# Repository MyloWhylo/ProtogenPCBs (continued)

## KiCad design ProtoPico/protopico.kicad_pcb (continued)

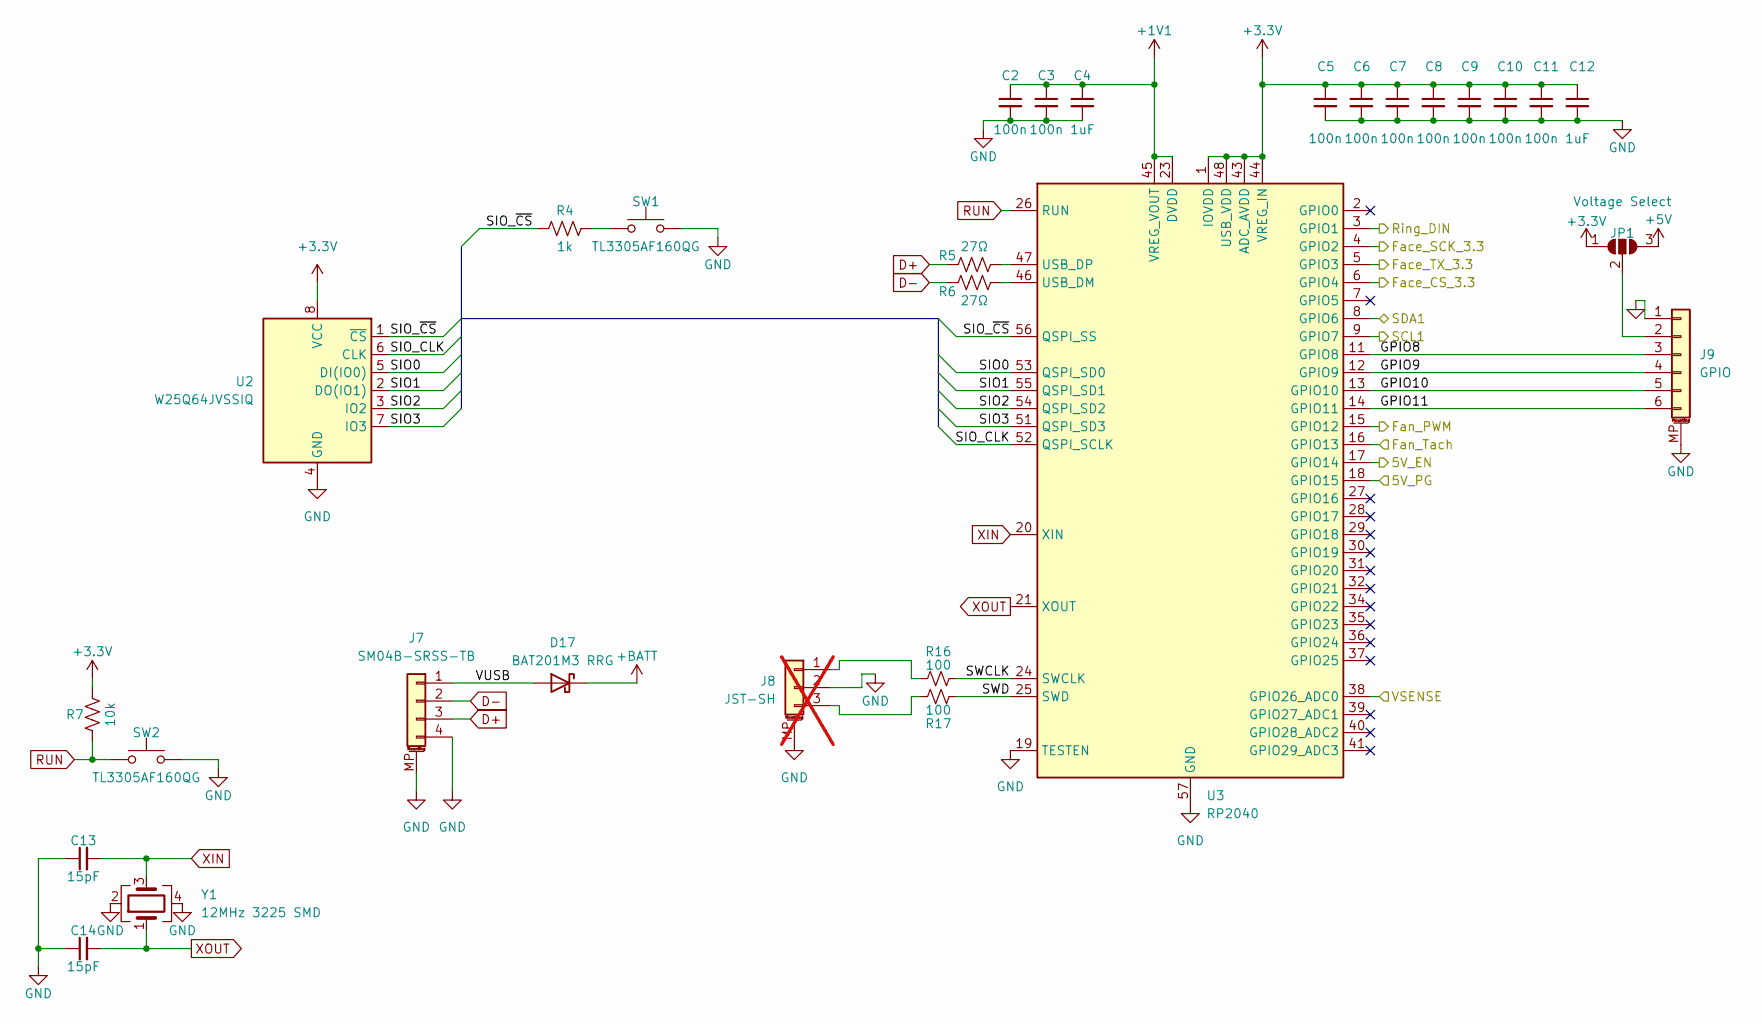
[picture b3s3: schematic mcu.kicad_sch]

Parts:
C2, C3, C5, C6, C7, C8, C9, C10, C11: 100n; C_0402_1005Metric
C4, C12: 1uF; C_0402_1005Metric
C13, C14: 15pF; C_0402_1005Metric
D17: BAT201M3 RRG; D_SOD-323_HandSoldering
J7: SM04B-SRSS-TB; JST_PH_S4B-PH-SM4-TB_1x04-1MP_P2.00mm_Horizontal
J8: JST-SH; JST_SH_SM03B-SRSS-TB_1x03-1MP_P1.00mm_Horizontal; not fitted
J9: GPIO; JST_GH_SM06B-GHS-TB_1x06-1MP_P1.25mm_Horizontal
JP1: Voltage Select; SolderJumper-3_P1.3mm_Open_RoundedPad1.0x1.5mm
R4: 1k; R_0805_2012Metric
R5, R6: 27Ω; R_0402_1005Metric
R7: 10k; R_0402_1005Metric
R16, R17: 100; R_0402_1005Metric
SW1, SW2: TL3305AF160QG; SW_SPST_TL3305A
U2: W25Q64JVSSIQ; SOIC-8_5.23x5.23mm_P1.27mm
U3: RP2040; QFN-56-1EP_7x7mm_P0.4mm_EP3.2x3.2mm
Y1: 12MHz 3225 SMD; Crystal_SMD_3225-4Pin_3.2x2.5mm

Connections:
5V_EN: U3.17 (GPIO14); also elsewhere on the board
5V_PG: U3.18 (GPIO15); also elsewhere on the board
+1V1: C2.1, C3.1, C4.1, U3.23 (DVDD), U3.45 (VREG_VOUT), U3.50 (DVDD)
+3.3V: C5.1, C6.1, C7.1, C8.1, C9.1, C10.1, C11.1, C12.1, JP1.1 (A), R7.2, U2.8 (VCC), U3.1 (IOVDD), U3.10 (IOVDD), U3.22 (IOVDD), U3.33 (IOVDD), U3.42 (IOVDD), U3.43 (ADC_AVDD), U3.44 (VREG_IN), U3.48 (USB_VDD), U3.49 (IOVDD); also elsewhere on the board
+5V: JP1.3 (B); also elsewhere on the board
+BATT: D17.1 (K); also elsewhere on the board
/Microcontroller/GPIO8: J9.3, U3.11 (GPIO8)
/Microcontroller/GPIO9: J9.4, U3.12 (GPIO9)
/Microcontroller/GPIO10: J9.5, U3.13 (GPIO10)
/Microcontroller/GPIO11: J9.6, U3.14 (GPIO11)
/Microcontroller/SIO0: U2.5 (DI(IO0)), U3.53 (QSPI_SD0)
/Microcontroller/SIO1: U2.2 (DO(IO1)), U3.55 (QSPI_SD1)
/Microcontroller/SIO2: U2.3 (IO2), U3.54 (QSPI_SD2)
/Microcontroller/SIO3: U2.7 (IO3), U3.51 (QSPI_SD3)
/Microcontroller/SIO_CLK: U2.6 (CLK), U3.52 (QSPI_SCLK)
/Microcontroller/SIO_~CS: R4.1, U2.1 (~CS), U3.56 (QSPI_SS)
/Microcontroller/SWCLK: R16.2, U3.24 (SWCLK)
/Microcontroller/SWD: R17.2, U3.25 (SWD)
/Microcontroller/VUSB: D17.2 (A), J7.1
D+: J7.3, R5.1
D-: J7.2, R6.1
Face CS_3.3: U3.6 (GPIO4); also elsewhere on the board
Face SCK_3.3: U3.4 (GPIO2); also elsewhere on the board
Face TX_3.3: U3.5 (GPIO3); also elsewhere on the board
Fan PWM: U3.15 (GPIO12); also elsewhere on the board
Fan Tach: U3.16 (GPIO13); also elsewhere on the board
GND: C2.2, C3.2, C4.2, C5.2, C6.2, C7.2, C8.2, C9.2, C10.2, C11.2, C12.2, C13.1, C14.1, J7.4, J7.MP (MountPin), J8.2, J8.MP (MountPin), J9.1, J9.MP (MountPin), SW1.2, SW2.2, U2.4 (GND), U3.19 (TESTEN), U3.57 (GND), Y1.2, Y1.4; also elsewhere on the board
unnamed: J8.1, R16.1
unnamed: J8.3, R17.1
unnamed: J9.2, JP1.2 (C)
unnamed: R4.2, SW1.1
unnamed: R6.2, U3.46 (USB_DM)
unnamed: R5.2, U3.47 (USB_DP)
RUN: R7.1, SW2.1, U3.26 (RUN)
Ring DIN: U3.3 (GPIO1); also elsewhere on the board
SCL1: U3.9 (GPIO7); also elsewhere on the board
SDA1: U3.8 (GPIO6); also elsewhere on the board
VSENSE: U3.38 (GPIO26_ADC0); also elsewhere on the board
XIN: C13.2, U3.20 (XIN), Y1.3
XOUT: C14.2, U3.21 (XOUT), Y1.1

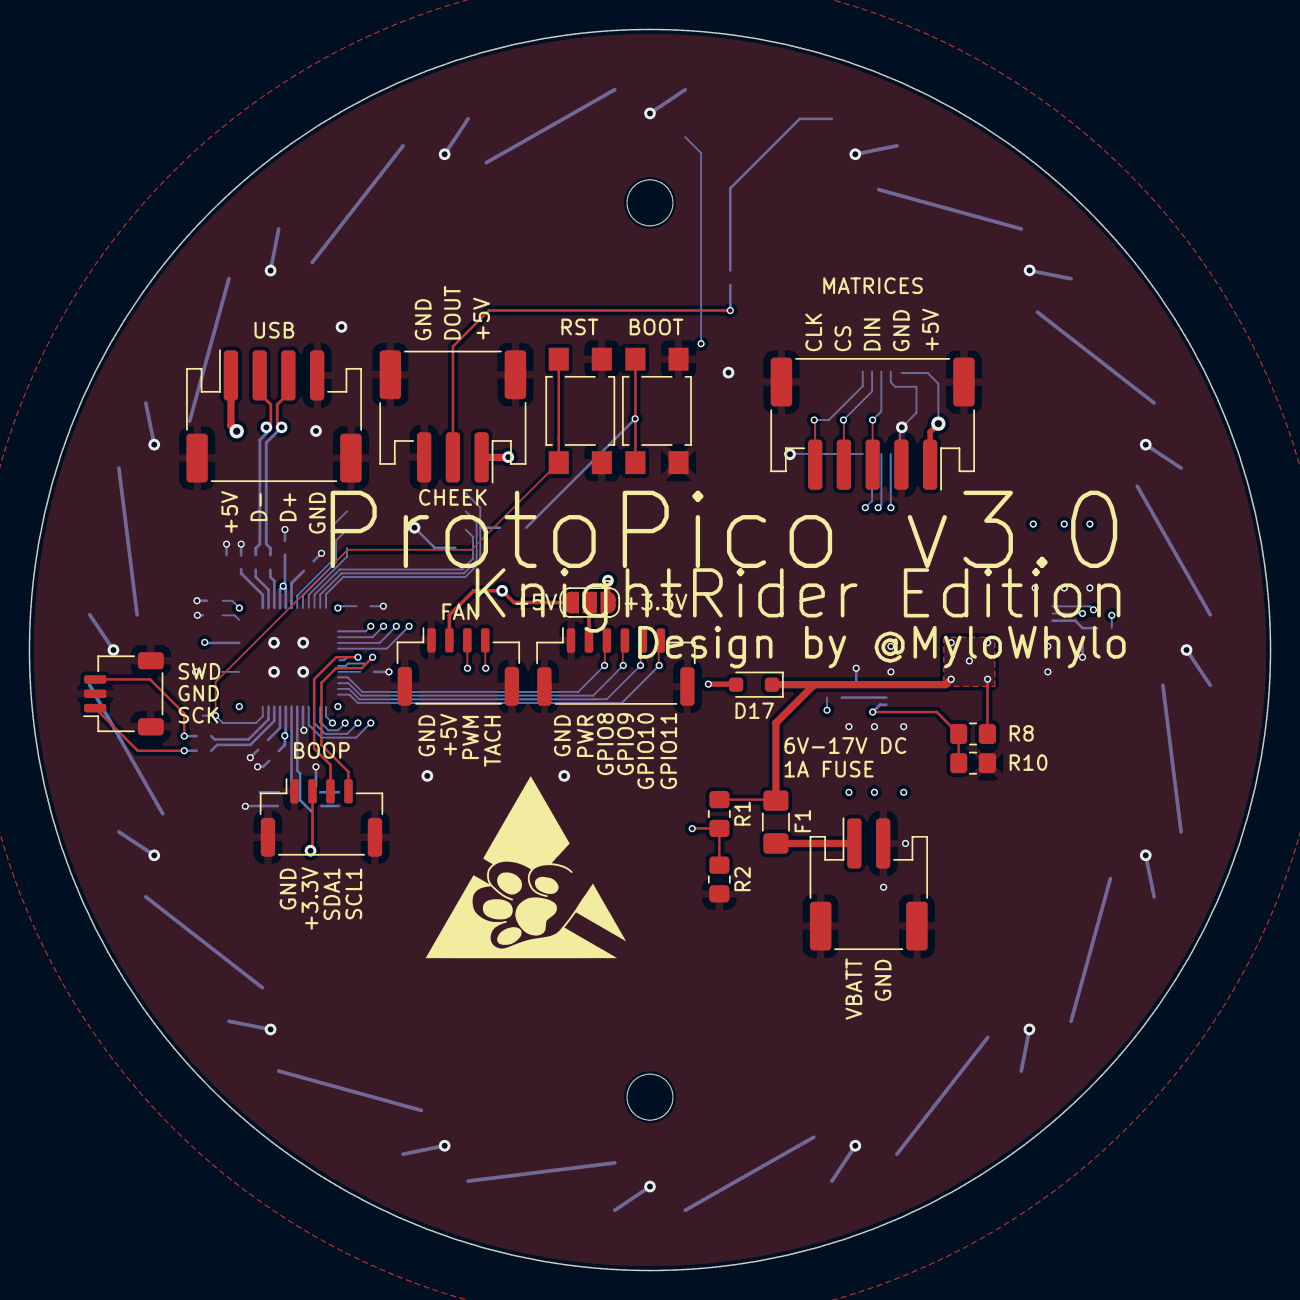
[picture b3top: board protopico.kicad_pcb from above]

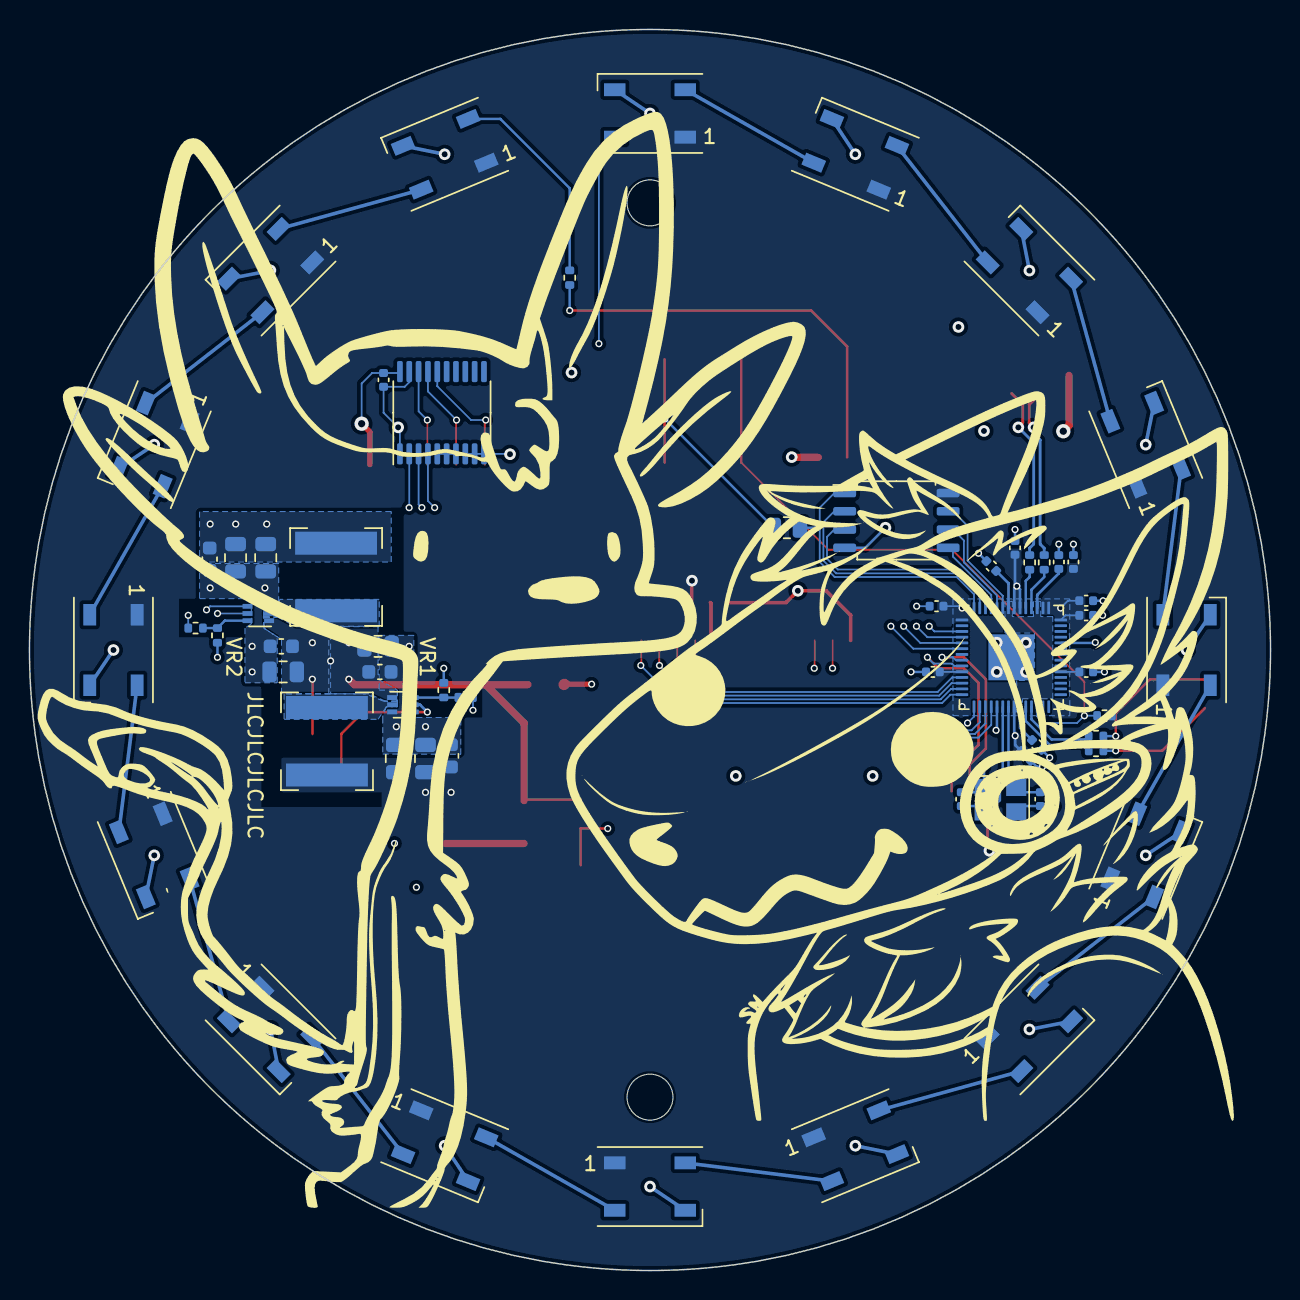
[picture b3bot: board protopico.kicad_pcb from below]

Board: 4 copper layers, 86.4 x 86.4 mm, 78 parts (61 on the bottom side), 66 nets.

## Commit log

2023-09-05 Update cheek pcb to Rev 2
2024-06-14 Update to V2 of Backpack
